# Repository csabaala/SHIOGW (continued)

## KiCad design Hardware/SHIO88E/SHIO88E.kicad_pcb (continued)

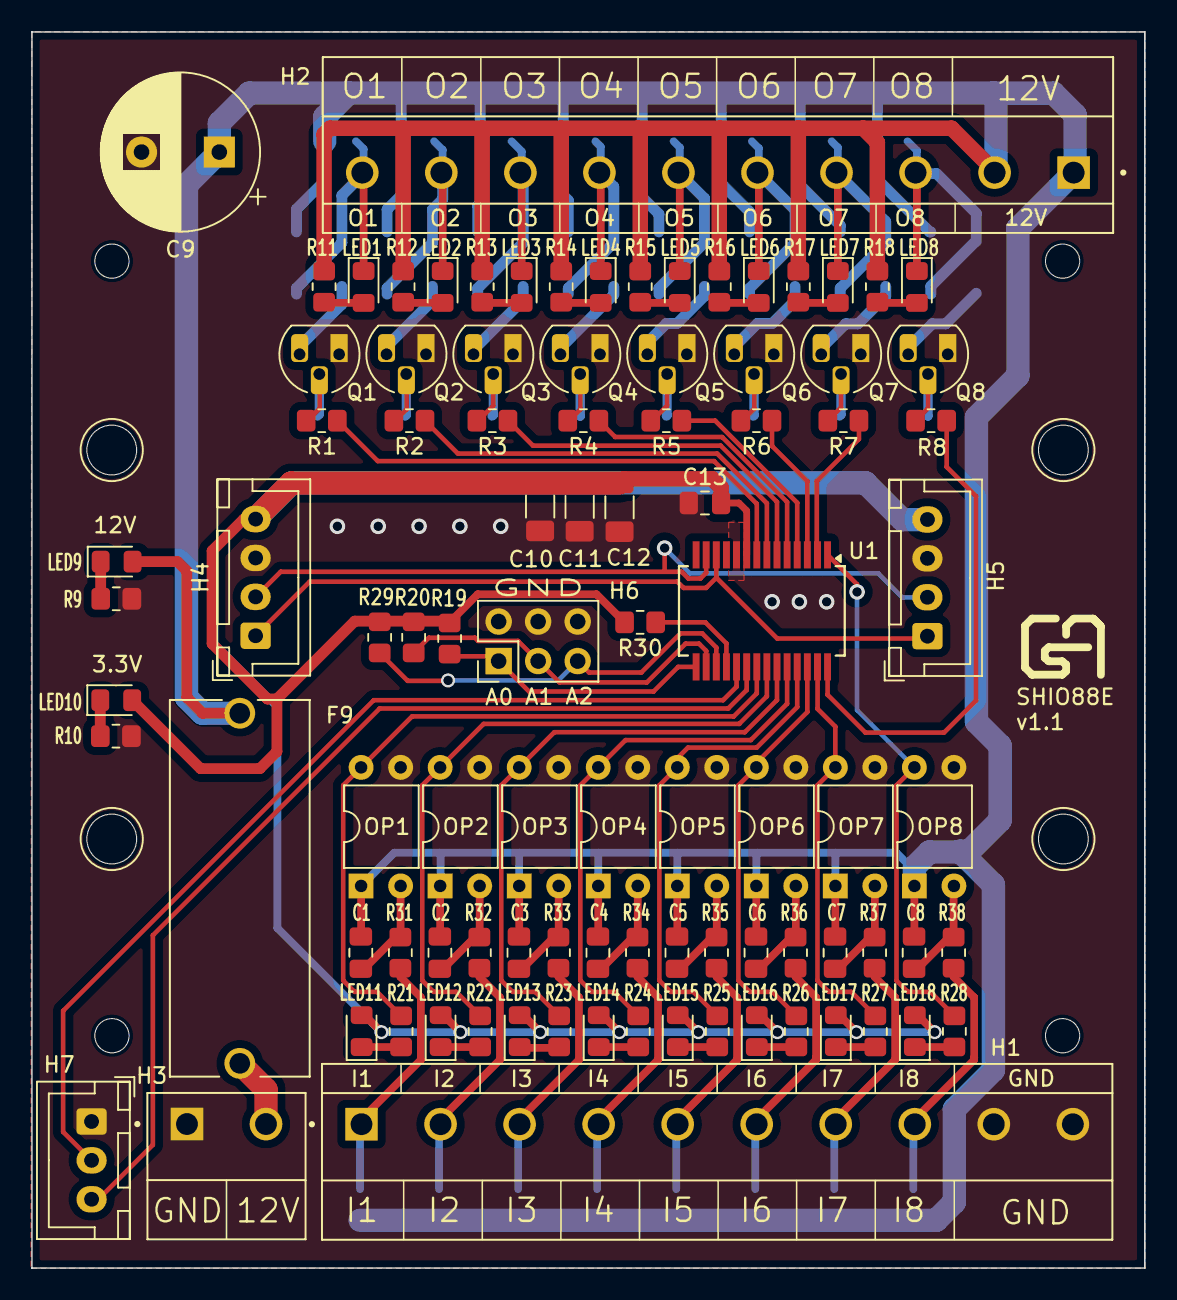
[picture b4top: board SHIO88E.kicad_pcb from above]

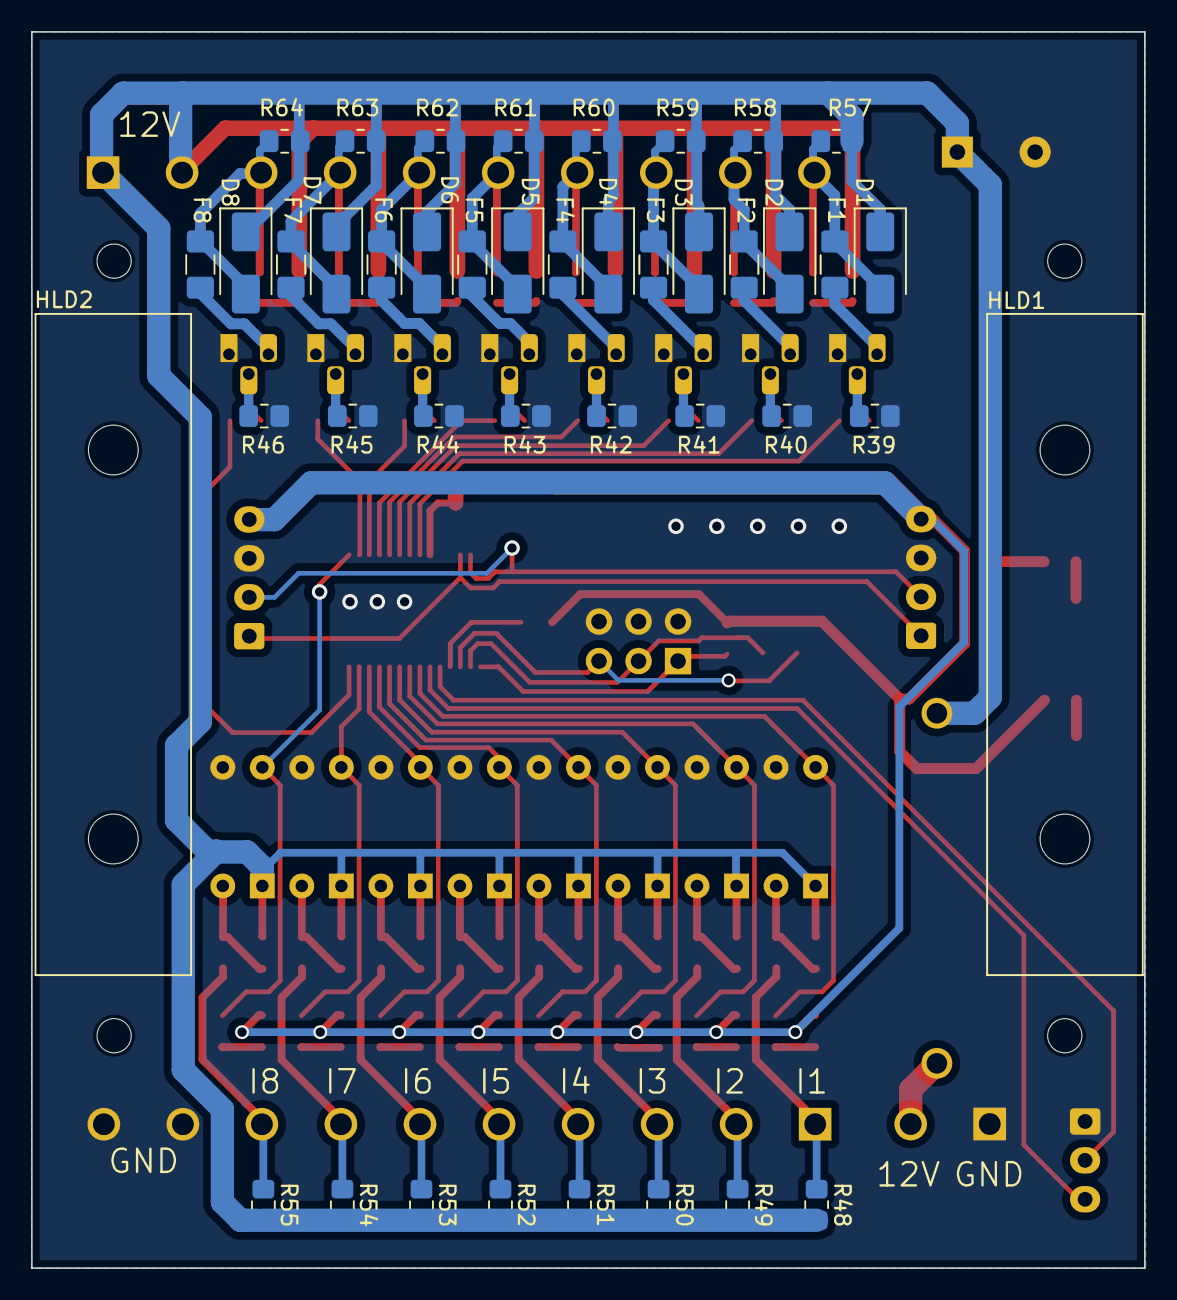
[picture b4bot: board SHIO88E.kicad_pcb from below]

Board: 2 copper layers, 71.5 x 79.5 mm, 136 parts (40 on the bottom side), 86 nets.

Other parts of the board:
HLD1, HLD2: DINRailAdapter_3xM3_PhoenixContact_1201578

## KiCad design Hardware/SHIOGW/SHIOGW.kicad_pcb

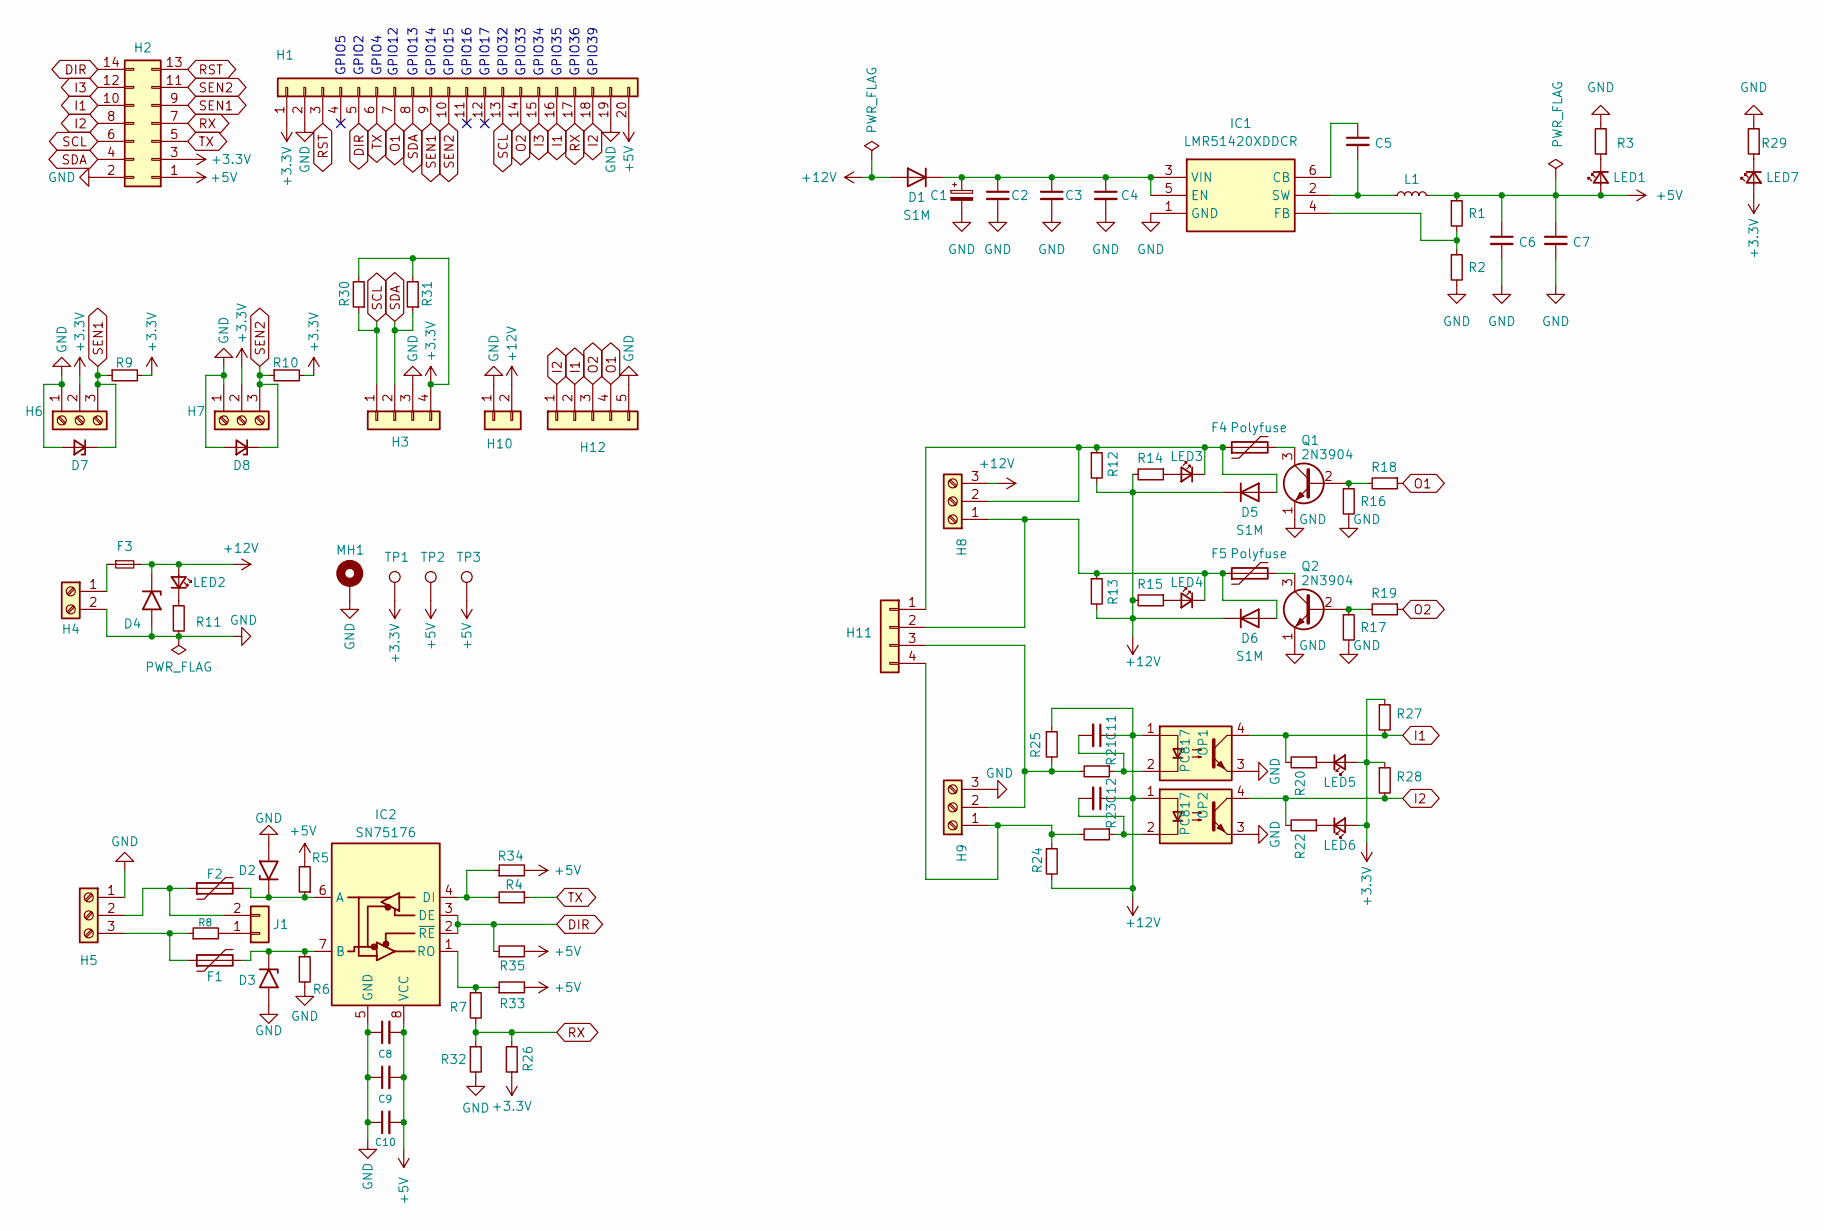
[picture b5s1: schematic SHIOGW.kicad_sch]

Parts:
C1: C_Polarized_Small; CP_Radial_D10.0mm_P5.00mm
C2, C3, C10: C_Small; C_1206_3216Metric_Pad1.33x1.80mm_HandSolder; LCSC C13585
C4: C_Small; C_1206_3216Metric_Pad1.33x1.80mm_HandSolder; LCSC C50254
C5, C8, C9: C_Small; C_0805_2012Metric_Pad1.18x1.45mm_HandSolder; LCSC C49678
C6, C7: C_Small; C_1206_3216Metric_Pad1.33x1.80mm_HandSolder; LCSC C12891
C11, C12: C_Small; C_0805_2012Metric_Pad1.18x1.45mm_HandSolder; LCSC C1710
D1, D5, D6: S1M; D_SMA; LCSC C412437
D2, D3: SMBJ12CA; D_SMB; LCSC C353397
D4: SMBJ28CA; D_SMB; LCSC C353369
D7, D8: D_Zener_Small; Nexperia_CFP3_SOD-123W; LCSC C2903912
F1, F2, F4, F5: Polyfuse; Fuse_1206_3216Metric_Pad1.42x1.75mm_HandSolder; LCSC C2830235
F3: Fuse_Small; FUSE_holder
H1: Conn_01x20; PinSocket_1x20_P2.54mm_Vertical
H2: Conn_02x07_Odd_Even; IDC-Header_2x07_P2.54mm_Vertical
H3, H11: Conn_01x04; JST_XH_B4B-XH-A_1x04_P2.50mm_Vertical
H4: Screw_Terminal_01x02; MSTB 2,5-2-G-5,08
H5, H6, H7, H8, H9: Screw_Terminal_01x03; TerminalBlock_MSTB 2,5 3-G-5,08_v3
H10: Conn_01x02; JST_XH_S2B-XH-A-1_1x02_P2.50mm_Horizontal
H12: Conn_01x05; PinHeader_1x05_P2.54mm_Vertical
IC1: LMR51420XDDCR; LMR51420; Mouser Part Number 595-LMR51420XDDCR
IC2: SN75176; DIP-8_W7.62mm
J1: Conn_01x02; PinHeader_1x02_P2.54mm_Vertical
L1: L_Small; L_Chilisin_BMRx00060630; LCSC C497872
LED1, LED2, LED7: LED_Small; LED_0805_2012Metric_Pad1.15x1.40mm_HandSolder; LCSC C2296
LED3, LED4, LED5, LED6: LED_Small; LED_0805_2012Metric_Pad1.15x1.40mm_HandSolder; LCSC C84256
MH1: MountingHole_Pad; MountingHole_3.2mm_M3_Pad_Via
OP1, OP2: PC817; PC817_custom
Q1, Q2: 2N3904; TO-92_HandSolder
R1: R_Small; R_0805_2012Metric_Pad1.20x1.40mm_HandSolder; LCSC C149504
R2: R_Small; R_0805_2012Metric_Pad1.20x1.40mm_HandSolder; LCSC C17448
R3: R_Small; R_0805_2012Metric_Pad1.20x1.40mm_HandSolder; LCSC C17661
R4: R_Small; R_0805_2012Metric_Pad1.20x1.40mm_HandSolder; LCSC C17408
R5, R6, R20, R21, R22, R23, R29: R_Small; R_0805_2012Metric_Pad1.20x1.40mm_HandSolder; LCSC C17520
R7, R9, R10: R_Small; R_0805_2012Metric_Pad1.20x1.40mm_HandSolder; LCSC C17673
R8: R_Small; R_0805_2012Metric_Pad1.20x1.40mm_HandSolder; LCSC C17437
R11, R14, R15, R16, R17, R27, R28, R32, R33, R34, R35: R_Small; R_0805_2012Metric_Pad1.20x1.40mm_HandSolder; LCSC C17414
R12, R13, R24, R25, R30, R31: R_Small; R_0805_2012Metric_Pad1.20x1.40mm_HandSolder
R18, R19, R26: R_Small; R_0805_2012Metric_Pad1.20x1.40mm_HandSolder; LCSC C17513
TP1, TP2, TP3: TestPoint; TestPoint_Pad_1.0x1.0mm_custom

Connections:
+3.3V: H1.1, H2.3, H3.4, H6.2, H7.2, LED5.2 (A), LED6.2 (A), LED7.2 (A), R9.2, R10.2, R26.1, R27.1, R28.1, R30.2, R31.2, TP1.1
+5V: C6.1, C7.1, C8.2, C9.2, C10.2, H1.20, H2.1, IC2.8 (VCC), L1.2, LED1.2 (A), R1.1, R5.2, R33.2, R34.2, R35.2, TP2.1, TP3.1
+12V: C11.1, C12.1, D1.2 (A), D4.1 (A1), D5.1 (K), D6.1 (K), F3.2, H8.3, H10.2, LED2.2 (A), OP1.1, OP2.1, R12.2, R13.2, R14.2, R15.2, R24.2, R25.1
DIR: H1.5, H2.14, IC2.2 (~RE), IC2.3 (DE), R35.1
GND: C1.2, C2.2, C3.2, C4.2, C6.2, C7.2, C8.1, C9.1, C10.1, D2.2 (A2), D3.2 (A2), D4.2 (A2), D7.2 (A), D8.2 (A), H1.2, H1.19, H2.2, H3.3, H4.2, H5.1, H6.1, H7.1, H9.3, H10.1, H12.5, IC1.1 (GND), IC2.5 (GND), MH1.1, OP1.3, OP2.3, Q1.1 (E), Q2.1 (E), R2.2, R3.2, R6.2, R11.2, R16.2, R17.2, R29.2, R32.2
I1: H1.16, H2.10, H12.2, OP1.4, R20.2, R27.2
I2: H1.18, H2.8, H12.1, OP2.4, R22.2, R28.2
I3: H1.15, H2.12
unnamed: C11.2, OP1.2, R21.1
unnamed: C12.2, OP2.2, R23.1
unnamed: C1.1, C2.1, C3.1, C4.1, D1.1 (K), IC1.3 (VIN), IC1.5 (EN)
unnamed: D2.1 (A1), F2.2, IC2.6 (A), R5.1
unnamed: D3.1 (A1), F1.2, IC2.7 (B), R6.1
unnamed: D5.2 (A), F4.1, H8.2, H11.1, LED3.1 (K), R12.1
unnamed: D6.2 (A), F5.1, H8.1, H11.2, LED4.1 (K), R13.1
unnamed: F3.1, H4.1
unnamed: F2.1, H5.2, J1.2
unnamed: F1.1, H5.3, R8.1
unnamed: H9.2, H11.3, R21.2, R25.2
unnamed: H9.1, H11.4, R23.2, R24.1
unnamed: C5.1, IC1.6 (CB)
unnamed: IC1.4 (FB), R1.2, R2.1
unnamed: C5.2, IC1.2 (SW), L1.1
unnamed: IC2.4 (DI), R4.2, R34.1
unnamed: IC2.1 (RO), R7.1, R33.1
unnamed: J1.1, R8.2
unnamed: LED1.1 (K), R3.1
unnamed: LED2.1 (K), R11.1
unnamed: LED3.2 (A), R14.1
unnamed: LED4.2 (A), R15.1
unnamed: LED5.1 (K), R20.1
unnamed: LED6.1 (K), R22.1
unnamed: LED7.1 (K), R29.1
unnamed: Q1.2 (B), R16.1, R18.2
unnamed: F4.2, Q1.3 (C)
unnamed: Q2.2 (B), R17.1, R19.2
unnamed: F5.2, Q2.3 (C)
O1: H1.7, H12.4, R18.1
O2: H1.14, H12.3, R19.1
RST: H1.3, H2.13
RX: H1.17, H2.7, R7.2, R26.2, R32.1
SCL: H1.13, H2.6, H3.1, R30.1
SDA: H1.8, H2.4, H3.2, R31.1
SEN1: D7.1 (K), H1.9, H2.9, H6.3, R9.1
SEN2: D8.1 (K), H1.10, H2.11, H7.3, R10.1
TX: H1.6, H2.5, R4.1

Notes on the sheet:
GPIO39
GPIO33
GPIO14
GPIO35
GPIO32
GPIO2
GPIO15
GPIO34
GPIO36
GPIO4
GPIO12
GPIO17
GPIO5
GPIO16
GPIO13

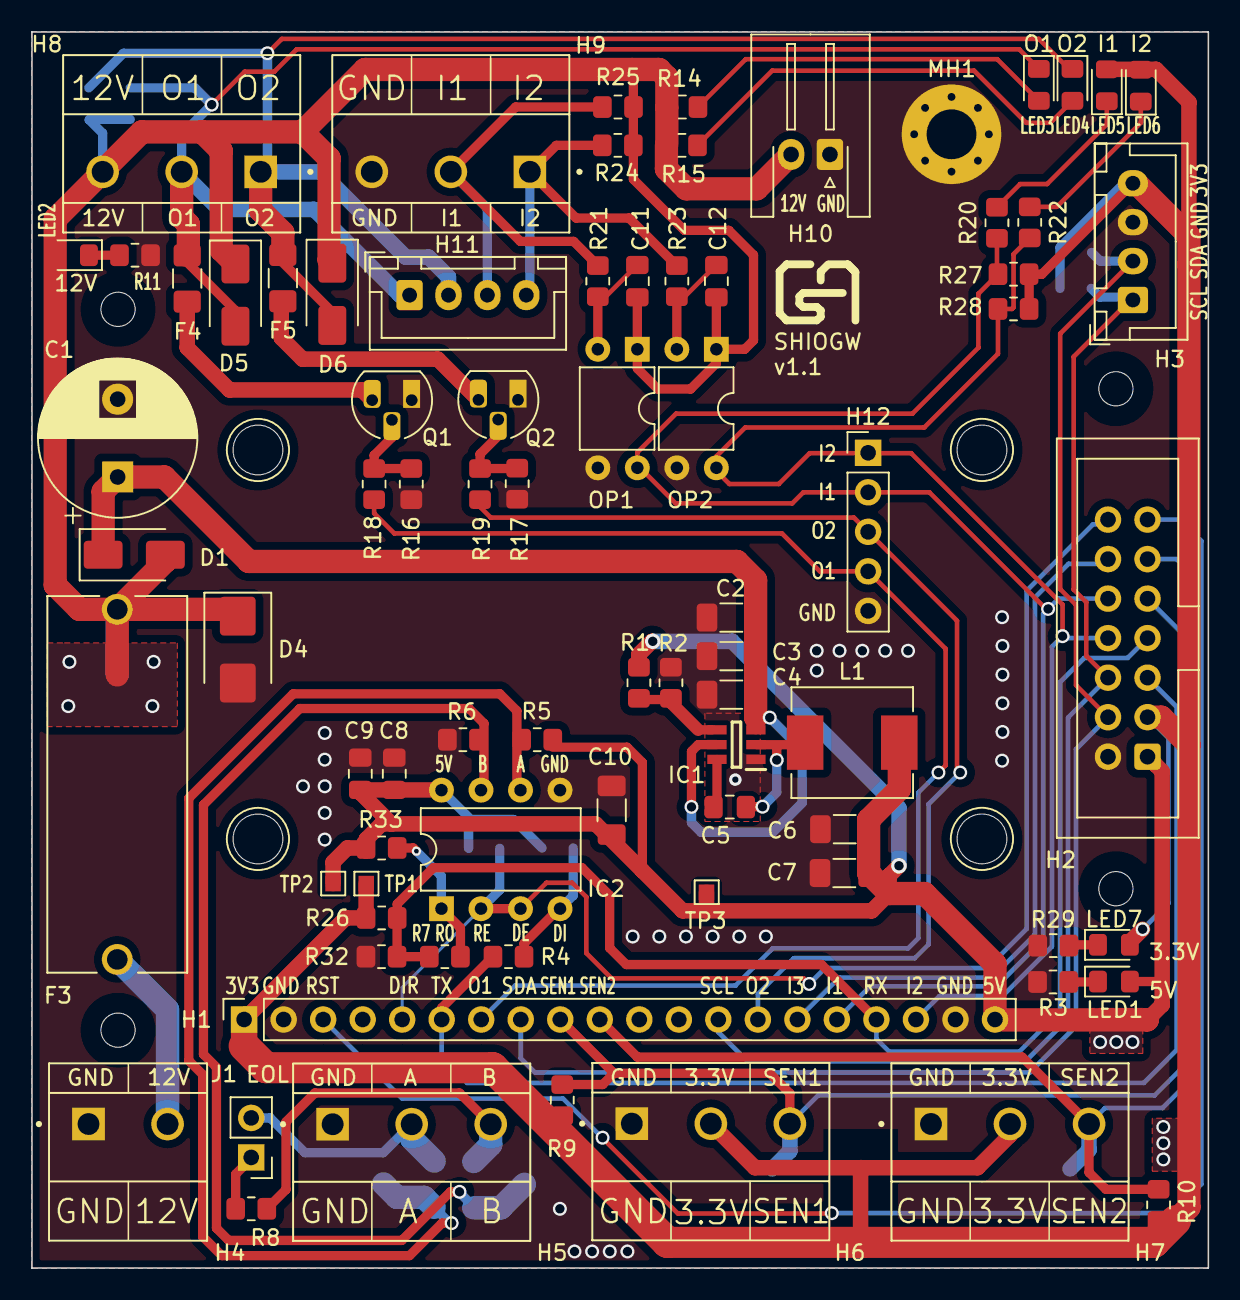
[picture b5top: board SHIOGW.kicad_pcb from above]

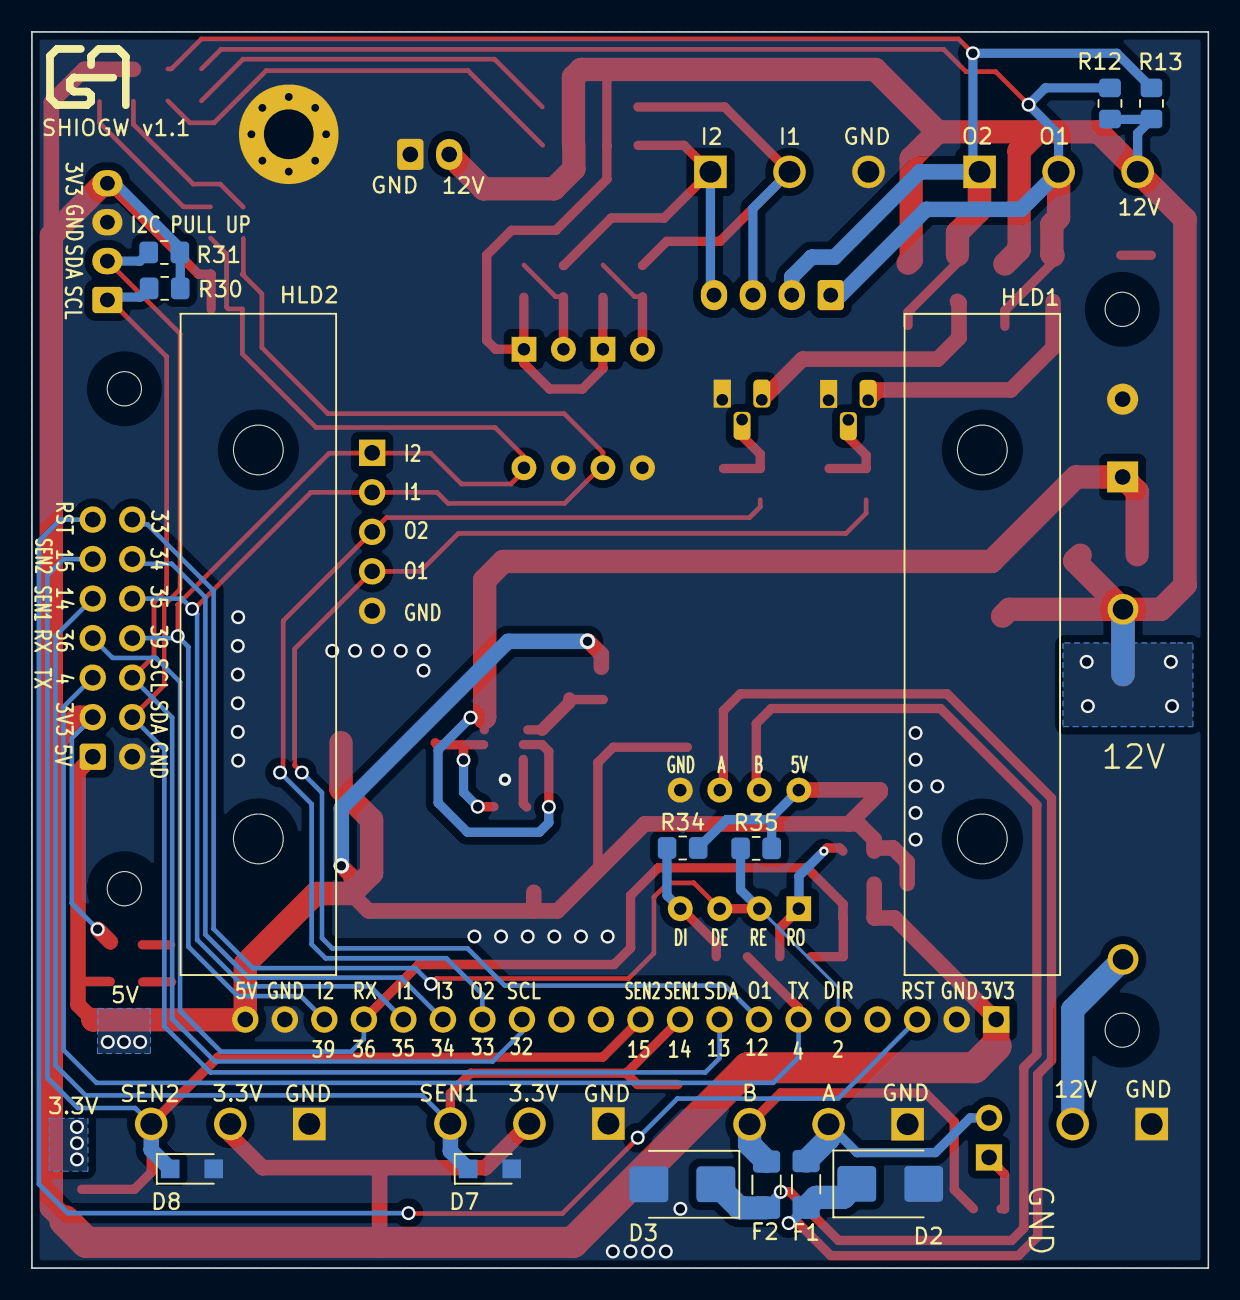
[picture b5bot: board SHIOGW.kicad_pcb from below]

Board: 2 copper layers, 75.6 x 79.5 mm, 93 parts (12 on the bottom side), 46 nets.

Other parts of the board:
HLD1, HLD2: DINRailAdapter_3xM3_PhoenixContact_1201578

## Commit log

2025-06-09 Create LICENSE
2025-12-10 GWHMI: updated symbol fields SHIO88E: fixed silkscreen texts
2026-01-28 Added LRMNT and SHIOADS boards
2026-02-15 added fp-lib-table files
